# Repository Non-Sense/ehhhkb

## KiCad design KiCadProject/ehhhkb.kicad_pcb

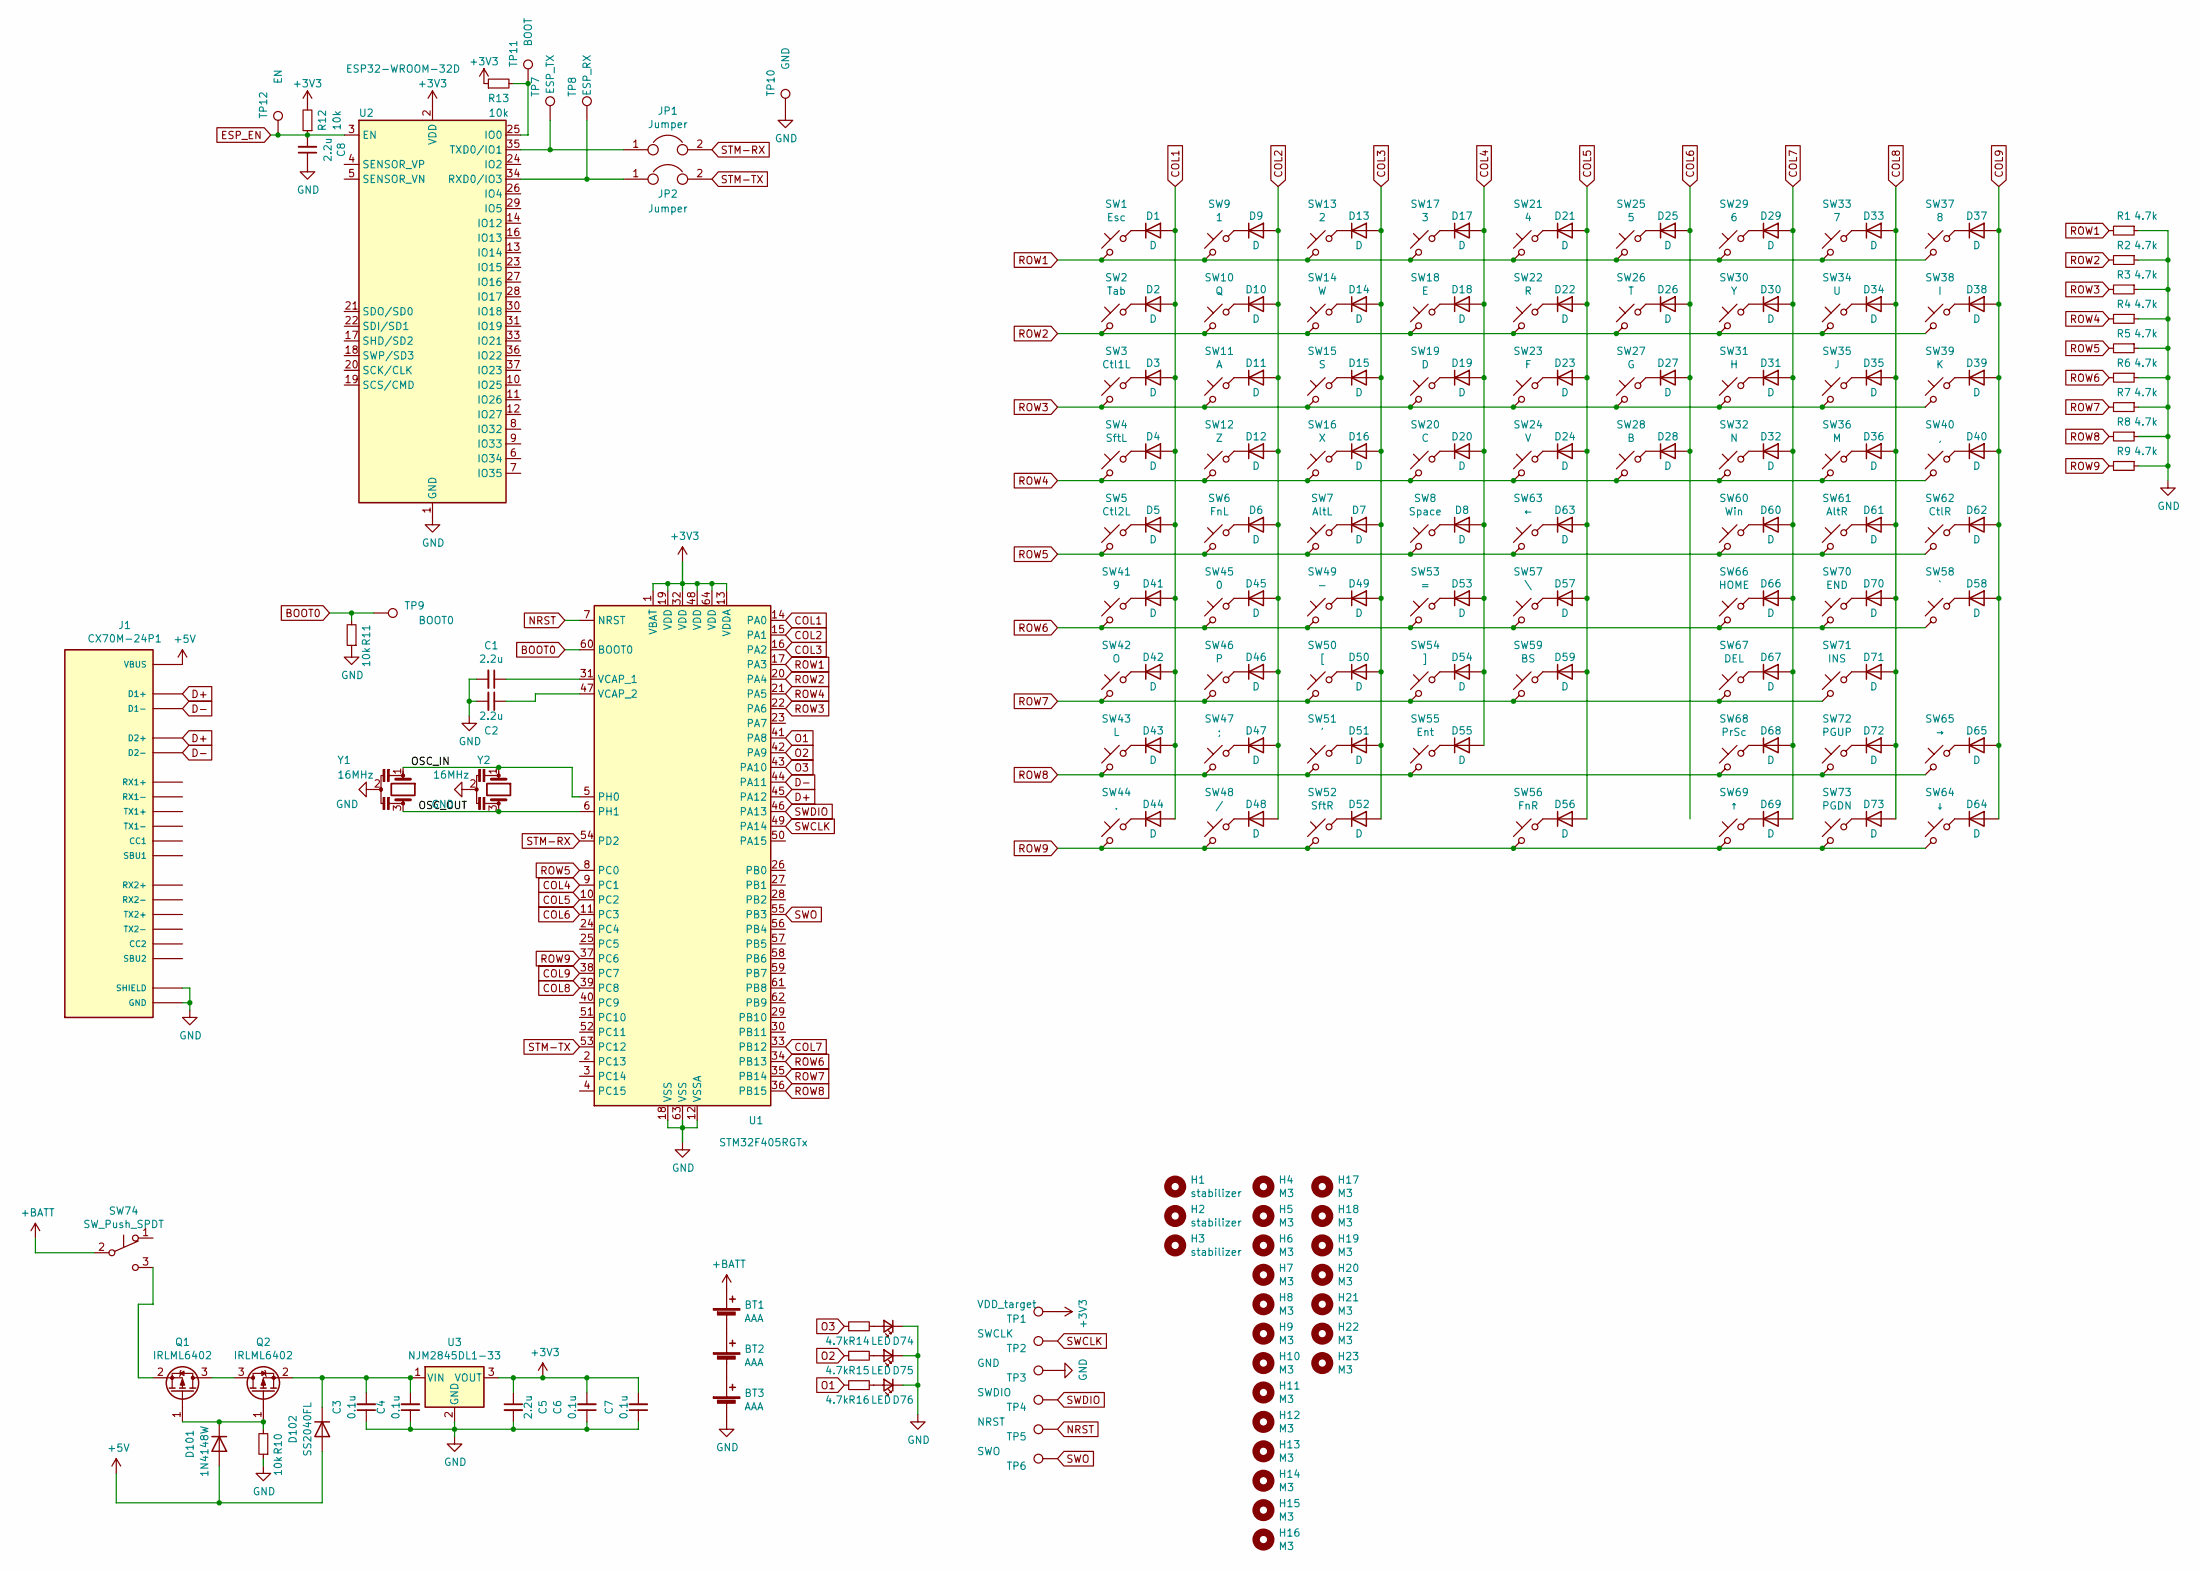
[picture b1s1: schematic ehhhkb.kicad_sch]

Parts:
BT1, BT2, BT3: AAA; AAAx1
C1, C2, C5, C8: 2.2u; C_0603_1608Metric
C3, C4, C6, C7: 0.1u; C_0603_1608Metric
D1, D2, D3, D4, D5, D6, D7, D8, D9, D10, D11, D12, D13, D14, D15, D16, D17, D18, D19, D20, D21, D22, D23, D24, D25, D26, D27, D28, D29, D30, D31, D32, D33, D34, D35, D36, D37, D38, D39, D40, D41, D42, D43, D44, D45, D46, D47, D48, D49, D50, D51, D52, D53, D54, D55, D56, D57, D58, D59, D60, D61, D62, D63, D64, D65, D66, D67, D68, D69, D70, D71, D72, D73: D; D_SOD-123
D74, D75, D76: LED; LED_0603_1608Metric_Pad1.05x0.95mm_HandSolder
D101: 1N4148W; D_SOD-123
D102: SS2040FL; D_SOD-123
H1, H2: stabilizer; Stabilizer_Cherry_MX_2u
H3: stabilizer; Stabilizer_Cherry_MX_6.25u
H4, H5, H6, H7, H8, H9, H10, H11, H12, H13, H14, H15, H16, H17, H18, H19, H20, H21, H22, H23: M3; MountingHole_2.2mm_M2
J1: CX70M-24P1; HRS_CX70M-24P1
JP1, JP2: Jumper; SolderJumper-2_P1.3mm_Open_Pad1.0x1.5mm
Q1, Q2: IRLML6402; SOT-23
R1, R2, R3, R4, R5, R6, R7, R8, R9, R14, R15, R16: 4.7k; R_0603_1608Metric
R10, R11, R12, R13: 10k; R_0603_1608Metric
SW1: Esc; Kailh_socket_MX_optional
SW2: Tab; Kailh_socket_MX_optional
SW3: Ctl1L; Kailh_socket_MX_optional
SW4: SftL; Kailh_socket_MX_optional
SW5: Ctl2L; Kailh_socket_MX_optional
SW6: FnL; Kailh_socket_MX_optional
SW7: AltL; Kailh_socket_MX_optional
SW8: Space; Kailh_socket_MX_optional
SW9: 1; Kailh_socket_MX_optional
SW10: Q; Kailh_socket_MX_optional
SW11: A; Kailh_socket_MX_optional
SW12: Z; Kailh_socket_MX_optional
SW13: 2; Kailh_socket_MX_optional
SW14: W; Kailh_socket_MX_optional
SW15: S; Kailh_socket_MX_optional
SW16: X; Kailh_socket_MX_optional
SW17: 3; Kailh_socket_MX_optional
SW18: E; Kailh_socket_MX_optional
SW19: D; Kailh_socket_MX_optional
SW20: C; Kailh_socket_MX_optional
SW21: 4; Kailh_socket_MX_optional
SW22: R; Kailh_socket_MX_optional
SW23: F; Kailh_socket_MX_optional
SW24: V; Kailh_socket_MX_optional
SW25: 5; Kailh_socket_MX_optional
SW26: T; Kailh_socket_MX_optional
SW27: G; Kailh_socket_MX_optional
SW28: B; Kailh_socket_MX_optional
SW29: 6; Kailh_socket_MX_optional
SW30: Y; Kailh_socket_MX_optional
SW31: H; Kailh_socket_MX_optional
SW32: N; Kailh_socket_MX_optional
SW33: 7; Kailh_socket_MX_optional
SW34: U; Kailh_socket_MX_optional
SW35: J; Kailh_socket_MX_optional
SW36: M; Kailh_socket_MX_optional
SW37: 8; Kailh_socket_MX_optional
SW38: I; Kailh_socket_MX_optional
SW39: K; Kailh_socket_MX_optional
SW40: ,; Kailh_socket_MX_optional
SW41: 9; Kailh_socket_MX_optional
SW42: O; Kailh_socket_MX_optional
SW43: L; Kailh_socket_MX_optional
SW44: .; Kailh_socket_MX_optional
SW45: 0; Kailh_socket_MX_optional
SW46: P; Kailh_socket_MX_optional
SW47: ;; Kailh_socket_MX_optional
SW48: /; Kailh_socket_MX_optional
SW49: -; Kailh_socket_MX_optional
SW50: [; Kailh_socket_MX_optional
SW51: '; Kailh_socket_MX_optional
SW52: SftR; Kailh_socket_MX_optional
SW53: =; Kailh_socket_MX_optional
SW54: ]; Kailh_socket_MX_optional
SW55: Ent; Kailh_socket_MX_optional
SW56: FnR; Kailh_socket_MX_optional
SW57: \; Kailh_socket_MX_optional
SW58: `; Kailh_socket_MX_optional
SW59: BS; Kailh_socket_MX_optional
SW60: Win; Kailh_socket_MX_optional
SW61: AltR; Kailh_socket_MX_optional
SW62: CtlR; Kailh_socket_MX_optional
SW63: ←; Kailh_socket_MX_optional
SW64: ↓; Kailh_socket_MX_optional
SW65: →; Kailh_socket_MX_optional
SW66: HOME; Kailh_socket_MX_optional
SW67: DEL; Kailh_socket_MX_optional
SW68: PrSc; Kailh_socket_MX_optional
SW69: ↑; Kailh_socket_MX_optional
SW70: END; Kailh_socket_MX_optional
SW71: INS; Kailh_socket_MX_optional
SW72: PGUP; Kailh_socket_MX_optional
SW73: PGDN; Kailh_socket_MX_optional
SW74: SW_Push_SPDT; JST_XH_B3B-XH-A_1x03_P2.50mm_Vertical
TP1: VDD_target; tp
TP2: SWCLK; tp
TP3, TP10: GND; tp
TP4: SWDIO; tp
TP5: NRST; tp
TP6: SWO; tp
TP7: ESP_TX; tp
TP8: ESP_RX; tp
TP9: BOOT0; tp
TP11: BOOT; tp
TP12: EN; tp
U1: STM32F405RGTx; LQFP-64_10x10mm_P0.5mm
U2: ESP32-WROOM-32D; ESP32-WROOM-32
U3: NJM2845DL1-33; TO-252-2
Y1: 16MHz; Resonator_muRata_CSTLSxxxX-3Pin_W5.5mm_H3.0mm
Y2: 16MHz; Resonator_SMD_muRata_CSTxExxV-3Pin_3.0x1.1mm_HandSoldering

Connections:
+3V3: C5.1, C6.2, C7.2, R12.2, R13.1, TP1.1, U1.1 (VBAT), U1.13 (VDDA), U1.19 (VDD), U1.32 (VDD), U1.48 (VDD), U1.64 (VDD), U2.2 (VDD), U3.3 (VOUT)
+5V: D101.2 (A), D102.2 (A), J1.A4 (VBUS), J1.A9 (VBUS), J1.B4 (VBUS), J1.B9 (VBUS)
+BATT: BT1.1 (+), SW74.2 (B)
/OSC_IN: U1.5 (PH0), Y1.1, Y2.1
/OSC_OUT: U1.6 (PH1), Y1.3, Y2.3
BOOT0: R11.2, TP9.1, U1.60 (BOOT0)
COL1: D1.2 (A), D2.2 (A), D3.2 (A), D4.2 (A), D5.2 (A), D41.2 (A), D42.2 (A), D43.2 (A), D44.2 (A), U1.14 (PA0)
COL2: D6.2 (A), D9.2 (A), D10.2 (A), D11.2 (A), D12.2 (A), D45.2 (A), D46.2 (A), D47.2 (A), D48.2 (A), U1.15 (PA1)
COL3: D7.2 (A), D13.2 (A), D14.2 (A), D15.2 (A), D16.2 (A), D49.2 (A), D50.2 (A), D51.2 (A), D52.2 (A), U1.16 (PA2)
COL4: D8.2 (A), D17.2 (A), D18.2 (A), D19.2 (A), D20.2 (A), D53.2 (A), D54.2 (A), D55.2 (A), U1.9 (PC1)
COL5: D21.2 (A), D22.2 (A), D23.2 (A), D24.2 (A), D56.2 (A), D57.2 (A), D59.2 (A), D63.2 (A), U1.10 (PC2)
COL6: D25.2 (A), D26.2 (A), D27.2 (A), D28.2 (A), U1.11 (PC3)
COL7: D29.2 (A), D30.2 (A), D31.2 (A), D32.2 (A), D60.2 (A), D66.2 (A), D67.2 (A), D68.2 (A), D69.2 (A), U1.33 (PB12)
COL8: D33.2 (A), D34.2 (A), D35.2 (A), D36.2 (A), D61.2 (A), D70.2 (A), D71.2 (A), D72.2 (A), D73.2 (A), U1.39 (PC8)
COL9: D37.2 (A), D38.2 (A), D39.2 (A), D40.2 (A), D58.2 (A), D62.2 (A), D64.2 (A), D65.2 (A), U1.38 (PC7)
D+: J1.A6 (D1+), J1.B6 (D2+), U1.45 (PA12)
D-: J1.A7 (D1-), J1.B7 (D2-), U1.44 (PA11)
ESP_EN: C8.2, R12.1, TP12.1, U2.3 (EN)
GND: BT3.2 (-), C1.2, C2.2, C3.1, C4.1, C5.2, C6.1, C7.1, C8.1, D74.1 (K), D75.1 (K), D76.1 (K), J1.A1 (GND), J1.A12 (GND), J1.B1 (GND), J1.B12 (GND), J1.S1 (SHIELD), J1.S2 (SHIELD), J1.S3 (SHIELD), J1.S4 (SHIELD), J1.S5 (SHIELD), J1.S5.1 (SHIELD), J1.S6 (SHIELD), J1.S6.1 (SHIELD), R1.1, R2.1, R3.1, R4.1, R5.1, R6.1, R7.1, R8.1, R9.1, R10.1, R11.1, TP3.1, TP10.1, U1.12 (VSSA), U1.18 (VSS), U1.63 (VSS), U2.1 (GND), U2.15 (GND), U2.38 (GND), U2.39 (GND), U3.2 (GND), Y1.2, Y2.2
NRST: TP5.1, U1.7 (NRST)
unnamed: BT1.2 (-), BT2.1 (+)
unnamed: BT2.2 (-), BT3.1 (+)
unnamed: C1.1, U1.31 (VCAP_1)
unnamed: C2.1, U1.47 (VCAP_2)
unnamed: C3.2, C4.2, D102.1 (K), Q2.2 (S), U3.1 (VIN)
unnamed: D1.1 (K), SW1.1
unnamed: D2.1 (K), SW2.1
unnamed: D3.1 (K), SW3.1
unnamed: D4.1 (K), SW4.1
unnamed: D5.1 (K), SW5.1
unnamed: D6.1 (K), SW6.1
unnamed: D7.1 (K), SW7.1
unnamed: D8.1 (K), SW8.1
unnamed: D9.1 (K), SW9.1
unnamed: D10.1 (K), SW10.1
unnamed: D11.1 (K), SW11.1
unnamed: D12.1 (K), SW12.1
unnamed: D13.1 (K), SW13.1
unnamed: D14.1 (K), SW14.1
unnamed: D15.1 (K), SW15.1
unnamed: D16.1 (K), SW16.1
unnamed: D17.1 (K), SW17.1
unnamed: D18.1 (K), SW18.1
unnamed: D19.1 (K), SW19.1
unnamed: D20.1 (K), SW20.1
unnamed: D21.1 (K), SW21.1
unnamed: D22.1 (K), SW22.1
unnamed: D23.1 (K), SW23.1
unnamed: D24.1 (K), SW24.1
unnamed: D25.1 (K), SW25.1
unnamed: D26.1 (K), SW26.1
unnamed: D27.1 (K), SW27.1
unnamed: D28.1 (K), SW28.1
unnamed: D29.1 (K), SW29.1
unnamed: D30.1 (K), SW30.1
unnamed: D31.1 (K), SW31.1
unnamed: D32.1 (K), SW32.1
unnamed: D33.1 (K), SW33.1
unnamed: D34.1 (K), SW34.1
unnamed: D35.1 (K), SW35.1
unnamed: D36.1 (K), SW36.1
unnamed: D37.1 (K), SW37.1
unnamed: D38.1 (K), SW38.1
unnamed: D39.1 (K), SW39.1
unnamed: D40.1 (K), SW40.1
unnamed: D41.1 (K), SW41.1
unnamed: D42.1 (K), SW42.1
unnamed: D43.1 (K), SW43.1
unnamed: D44.1 (K), SW44.1
unnamed: D45.1 (K), SW45.1
unnamed: D46.1 (K), SW46.1
unnamed: D47.1 (K), SW47.1
unnamed: D48.1 (K), SW48.1
unnamed: D49.1 (K), SW49.1
unnamed: D50.1 (K), SW50.1
unnamed: D51.1 (K), SW51.1
unnamed: D52.1 (K), SW52.1
unnamed: D53.1 (K), SW53.1
unnamed: D54.1 (K), SW54.1
unnamed: D55.1 (K), SW55.1
unnamed: D56.1 (K), SW56.1
unnamed: D57.1 (K), SW57.1
unnamed: D58.1 (K), SW58.1
unnamed: D59.1 (K), SW59.1
unnamed: D60.1 (K), SW60.1
unnamed: D61.1 (K), SW61.1
unnamed: D62.1 (K), SW62.1
unnamed: D63.1 (K), SW63.1
unnamed: D64.1 (K), SW64.1
unnamed: D65.1 (K), SW65.1
unnamed: D66.1 (K), SW66.1
unnamed: D67.1 (K), SW67.1
unnamed: D68.1 (K), SW68.1
unnamed: D69.1 (K), SW69.1
unnamed: D70.1 (K), SW70.1
unnamed: D71.1 (K), SW71.1
unnamed: D72.1 (K), SW72.1
unnamed: D73.1 (K), SW73.1
unnamed: D74.2 (A), R14.2
unnamed: D75.2 (A), R15.2
unnamed: D76.2 (A), R16.2
unnamed: D101.1 (K), Q1.1 (G), Q2.1 (G), R10.2
unnamed: JP1.1, TP7.1, U2.35 (TXD0/IO1)
unnamed: JP2.1, TP8.1, U2.34 (RXD0/IO3)
unnamed: Q1.2 (S), SW74.3 (C)
unnamed: Q1.3 (D), Q2.3 (D)
unnamed: R13.2, TP11.1, U2.25 (IO0)
O1: R16.1, U1.41 (PA8)
O2: R15.1, U1.42 (PA9)
O3: R14.1, U1.43 (PA10)
ROW1: R1.2, SW1.2, SW9.2, SW13.2, SW17.2, SW21.2, SW25.2, SW29.2, SW33.2, SW37.2, U1.17 (PA3)
ROW2: R2.2, SW2.2, SW10.2, SW14.2, SW18.2, SW22.2, SW26.2, SW30.2, SW34.2, SW38.2, U1.20 (PA4)
ROW3: R3.2, SW3.2, SW11.2, SW15.2, SW19.2, SW23.2, SW27.2, SW31.2, SW35.2, SW39.2, U1.22 (PA6)
ROW4: R4.2, SW4.2, SW12.2, SW16.2, SW20.2, SW24.2, SW28.2, SW32.2, SW36.2, SW40.2, U1.21 (PA5)
ROW5: R5.2, SW5.2, SW6.2, SW7.2, SW8.2, SW60.2, SW61.2, SW62.2, SW63.2, U1.8 (PC0)
ROW6: R6.2, SW41.2, SW45.2, SW49.2, SW53.2, SW57.2, SW58.2, SW66.2, SW70.2, U1.34 (PB13)
ROW7: R7.2, SW42.2, SW46.2, SW50.2, SW54.2, SW59.2, SW67.2, SW71.2, U1.35 (PB14)
ROW8: R8.2, SW43.2, SW47.2, SW51.2, SW55.2, SW65.2, SW68.2, SW72.2, U1.36 (PB15)
ROW9: R9.2, SW44.2, SW48.2, SW52.2, SW56.2, SW64.2, SW69.2, SW73.2, U1.37 (PC6)
STM-RX: JP1.2, U1.54 (PD2)
STM-TX: JP2.2, U1.53 (PC12)
SWCLK: TP2.1, U1.49 (PA14)
SWDIO: TP4.1, U1.46 (PA13)
SWO: TP6.1, U1.55 (PB3)

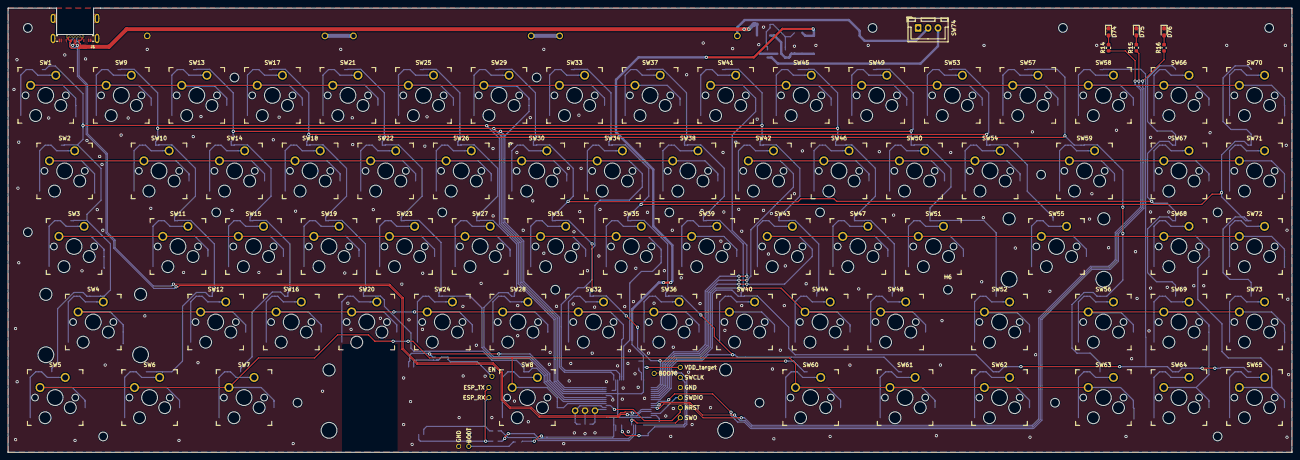
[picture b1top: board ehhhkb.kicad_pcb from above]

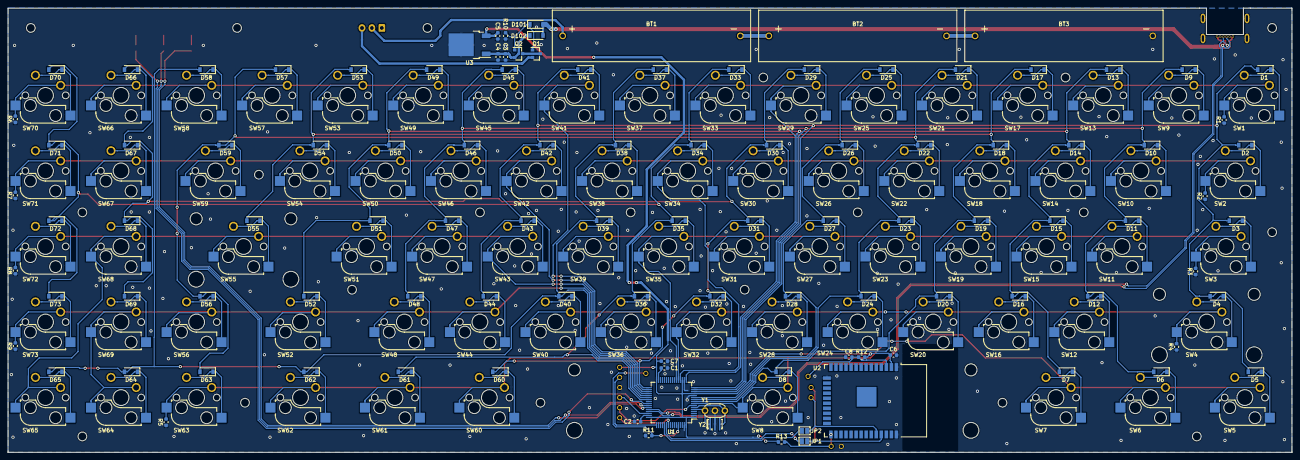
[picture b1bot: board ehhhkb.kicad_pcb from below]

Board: 2 copper layers, 323.8 x 112.0 mm, 224 parts (108 on the bottom side), 124 nets.

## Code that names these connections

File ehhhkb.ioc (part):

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Mcu.Name=STM32F405RGTx
Mcu.Package=LQFP64
Mcu.UserName=STM32F405RGTx
PA0-WKUP.GPIOParameters=GPIO_Speed,GPIO_Label
PA0-WKUP.GPIO_Label=COL1
PA0-WKUP.GPIO_Speed=GPIO_SPEED_FREQ_HIGH
PA0-WKUP.Signal=GPIO_Output
PA1.GPIOParameters=GPIO_Speed,GPIO_Label
PA1.GPIO_Label=COL2
PA1.GPIO_Speed=GPIO_SPEED_FREQ_HIGH
PA1.Signal=GPIO_Output
PA11.Mode=Device_Only
PA11.Signal=USB_OTG_FS_DM
PA12.Mode=Device_Only
PA12.Signal=USB_OTG_FS_DP
PA13.Mode=Trace_Asynchronous_SW
PA13.Signal=SYS_JTMS-SWDIO
PA14.Mode=Trace_Asynchronous_SW
PA14.Signal=SYS_JTCK-SWCLK
PA2.GPIOParameters=GPIO_Speed,GPIO_Label
PA2.GPIO_Label=COL3
PA2.GPIO_Speed=GPIO_SPEED_FREQ_HIGH
PA2.Signal=GPIO_Output
PA3.GPIOParameters=GPIO_PuPd,GPIO_Label
PA3.GPIO_Label=ROW1
PA3.GPIO_PuPd=GPIO_PULLDOWN
PA3.Signal=GPIO_Input
PA4.GPIOParameters=GPIO_PuPd,GPIO_Label
PA4.GPIO_Label=ROW2
PA4.GPIO_PuPd=GPIO_PULLDOWN
PA4.Signal=GPIO_Input
PA5.GPIOParameters=GPIO_PuPd,GPIO_Label
PA5.GPIO_Label=ROW4
PA5.GPIO_PuPd=GPIO_PULLDOWN
PA5.Signal=GPIO_Input
PA6.GPIOParameters=GPIO_PuPd,GPIO_Label
PA6.GPIO_Label=ROW3
PA6.GPIO_PuPd=GPIO_PULLDOWN
PA6.Signal=GPIO_Input
PB12.GPIOParameters=GPIO_Speed,GPIO_Label
PB12.GPIO_Label=COL7
PB12.GPIO_Speed=GPIO_SPEED_FREQ_HIGH
PB12.Signal=GPIO_Output
PB13.GPIOParameters=GPIO_PuPd,GPIO_Label
PB13.GPIO_Label=ROW6
PB13.GPIO_PuPd=GPIO_PULLDOWN
PB13.Signal=GPIO_Input
PB14.GPIOParameters=GPIO_PuPd,GPIO_Label
PB14.GPIO_Label=ROW7
PB14.GPIO_PuPd=GPIO_PULLDOWN
PB14.Signal=GPIO_Input
PB15.GPIOParameters=GPIO_PuPd,GPIO_Label
PB15.GPIO_Label=ROW8
PB15.GPIO_PuPd=GPIO_PULLDOWN
PB15.Signal=GPIO_Input
PB3.Mode=Trace_Asynchronous_SW
PB3.Signal=SYS_JTDO-SWO
PC0.GPIOParameters=GPIO_PuPd,GPIO_Label
PC0.GPIO_Label=ROW5
PC0.GPIO_PuPd=GPIO_PULLDOWN
PC0.Signal=GPIO_Input
PC1.GPIOParameters=GPIO_Speed,GPIO_Label
PC1.GPIO_Label=COL4
PC1.GPIO_Speed=GPIO_SPEED_FREQ_HIGH
PC1.Signal=GPIO_Output
PC12.Mode=Asynchronous
PC12.Signal=UART5_TX
PC2.GPIOParameters=GPIO_Speed,GPIO_Label
PC2.GPIO_Label=COL5
PC2.GPIO_Speed=GPIO_SPEED_FREQ_HIGH
PC2.Signal=GPIO_Output
PC3.GPIOParameters=GPIO_Speed,GPIO_Label
PC3.GPIO_Label=COL6
PC3.GPIO_Speed=GPIO_SPEED_FREQ_HIGH
PC3.Signal=GPIO_Output
PC6.GPIOParameters=GPIO_Label
PC6.GPIO_Label=ROW9
PC6.Signal=GPIO_Input
PC7.GPIOParameters=GPIO_Speed,GPIO_PuPd,GPIO_Label
PC7.GPIO_Label=COL9
PC7.GPIO_PuPd=GPIO_NOPULL
PC7.GPIO_Speed=GPIO_SPEED_FREQ_HIGH
PC7.Signal=GPIO_Output
PC8.GPIOParameters=GPIO_Speed,GPIO_PuPd,GPIO_Label
PC8.GPIO_Label=COL8
PC8.GPIO_PuPd=GPIO_NOPULL
PC8.GPIO_Speed=GPIO_SPEED_FREQ_HIGH
PC8.Signal=GPIO_Output
PD2.Mode=Asynchronous
PD2.Signal=UART5_RX
PH0-OSC_IN.Mode=HSE-External-Oscillator
PH0-OSC_IN.Signal=RCC_OSC_IN
PH1-OSC_OUT.Mode=HSE-External-Oscillator
PH1-OSC_OUT.Signal=RCC_OSC_OUT
RCC.HSE_VALUE=16000000
RCC.SYSCLKFreq_VALUE=96000000
RCC.SYSCLKSource=RCC_SYSCLKSOURCE_PLLCLK
board=custom

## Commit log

2021-10-01 initial
2021-10-02 nkro
2021-10-03 matrix
2021-10-13 fn key
2021-10-14 chattering
2021-10-15 layer hold
2024-09-07 kicad proj
